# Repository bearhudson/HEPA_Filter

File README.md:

The following is from Gemini based on source generated from Claude, so I have no idea if it's correct. I am not in any way versed in fluid dynamics enough to understand if this is correct, true, or even moderately sensible. I am going to make one, which should make it self evident if it works or not by checking the filter for dinge.

--------

# Series-Stacked HEPA Purifier (Dual 140mm)

A 3D-printed, high-efficiency room air purifier utilizing a cylindrical HEPA filter and two 140mm High Static Pressure (HSP) PC fans in a series-stacked configuration. 

If you've researched DIY air purifiers online, you've likely encountered a common claim: *"PC fans cannot push air through a HEPA filter because they don't generate enough static pressure."* 

This README breaks down the fluid dynamics and math proving why that claim is based on a misunderstanding of system impedance, and how series-stacking, swirl recovery, and acoustic tuning solve the problem.

---

## The Myth: "PC Fans Lack the Pressure for HEPA"

The skepticism online stems from comparing two mismatched static figures:
1. **The Filter's Rated Pressure Drop:** A standard pleated filter might list a pressure drop of $250 \text{ Pa}$ ($1.0 \text{ mmH}_2\text{O}$).
2. **The Fan's Rated Static Pressure:** A premium 140mm PC fan might max out at $25 \text{ Pa}$ ($2.5 \text{ mmH}_2\text{O}$).

If $25 \text{ Pa} < 250 \text{ Pa}$, the fan stalls, right? **Wrong.** 

This assumes the filter's pressure drop is a static, unchanging wall. In reality, a filter's resistance is a curve that depends entirely on airflow. The $250 \text{ Pa}$ rating is usually calculated at an HVAC system's flow rate of **300+ CFM**. We are targeting **40 to 60 CFM** for a single room.

### 1. The Math of Filter Resistance (System Impedance)
Airflow through the densely packed micro-glass fibers of a HEPA filter is strictly in the **laminar flow regime**. According to Darcy's Law for porous media, pressure drop ($\Delta P$) in laminar flow scales *linearly* with velocity (and therefore volumetric flow rate, $Q$):

$$ \Delta P = R \cdot Q $$

If a filter creates $250 \text{ Pa}$ of resistance at $300 \text{ CFM}$, we can find its resistance coefficient ($R$):

$$ R = \frac{250 \text{ Pa}}{300 \text{ CFM}} = 0.833 \text{ Pa/CFM} $$

If we only need $60 \text{ CFM}$ to achieve 4.5 Air Changes per Hour (ACH) in a 100 sq ft room, the actual pressure drop we must overcome is:

$$ \Delta P_{target} = 0.833 \cdot 60 = 50 \text{ Pa} $$

A single 140mm PC fan maxing out at $25 \text{ Pa}$ still cannot overcome this. This is where the series stack comes in.

### 2. The Math of Series Stacking
When fans are placed side-by-side (parallel), their volumetric flow ($Q$) adds together, but their pressure limit ($\Delta P$) remains the same. When fans are placed front-to-back (**series**), their volumetric flow remains the same, but their **static pressure limits add together**.

$$ \Delta P_{total} = \Delta P_1 + \Delta P_2 $$

Two $25 \text{ Pa}$ fans in series generate a maximum static pressure of **$50 \text{ Pa}$**. 

By plotting the combined fan curve (which slopes down as flow increases) against the filter's linear impedance curve (which slopes up as flow increases), the lines intersect at the **Operating Point**. Two 140mm HSP fans in series shift the pressure curve high enough to intersect the filter's impedance curve right at our $40 \text{-} 60 \text{ CFM}$ target.

---

## Aerodynamic Optimizations

Brute-forcing pressure isn't enough; the air must be managed efficiently to prevent turbulence and stalling. This design incorporates three specific aerodynamic features:

### The 12-Degree Diffuser
Air exiting the $94\text{ mm}$ inner bore of the filter must expand to hit the $132\text{ mm}$ swept area of the 140mm fans. If the transition is an abrupt flat step, flow separates, creating a low-pressure vortex that acts like a solid wall, artificially increasing system impedance. 
* This design uses a **$12^\circ$ half-angle conical diffuser**. Fluid dynamics dictates that a divergence angle under $15^\circ$ prevents boundary layer separation, allowing kinetic energy to efficiently convert back to static pressure before hitting the first fan.

### The Swirl Straightener
Axial fans impart a corkscrew rotation (swirl) to the air. If Fan 1 feeds directly into Fan 2, Fan 2's blades are hitting air that is already rotating in the same direction. This effectively reduces Fan 2's relative angle of attack to zero, rendering it useless. 
* Between the two fans is a **16mm deep, 13-vane stator**. It recovers the rotational kinetic energy of Fan 1, converting it into axial static pressure, and feeds non-rotating air into Fan 2 so it can bite the air and multiply the pressure curve properly. (13 is a prime number to prevent harmonic tonal resonance with standard 7- or 9-blade fan rotors).

### Acoustic Tuning (PWM Offset)
When two identical motors spin at the exact same RPM in a shared structural tube, they drift in and out of phase, creating a loud, pulsing harmonic hum (beating). 
* The custom ESP32 firmware drives the two fans on independent PWM channels. Fan 2 is mathematically offset to run **10% faster** than Fan 1. This prevents phase-locking and completely eliminates the beating frequency, resulting in a smooth, steady white noise.

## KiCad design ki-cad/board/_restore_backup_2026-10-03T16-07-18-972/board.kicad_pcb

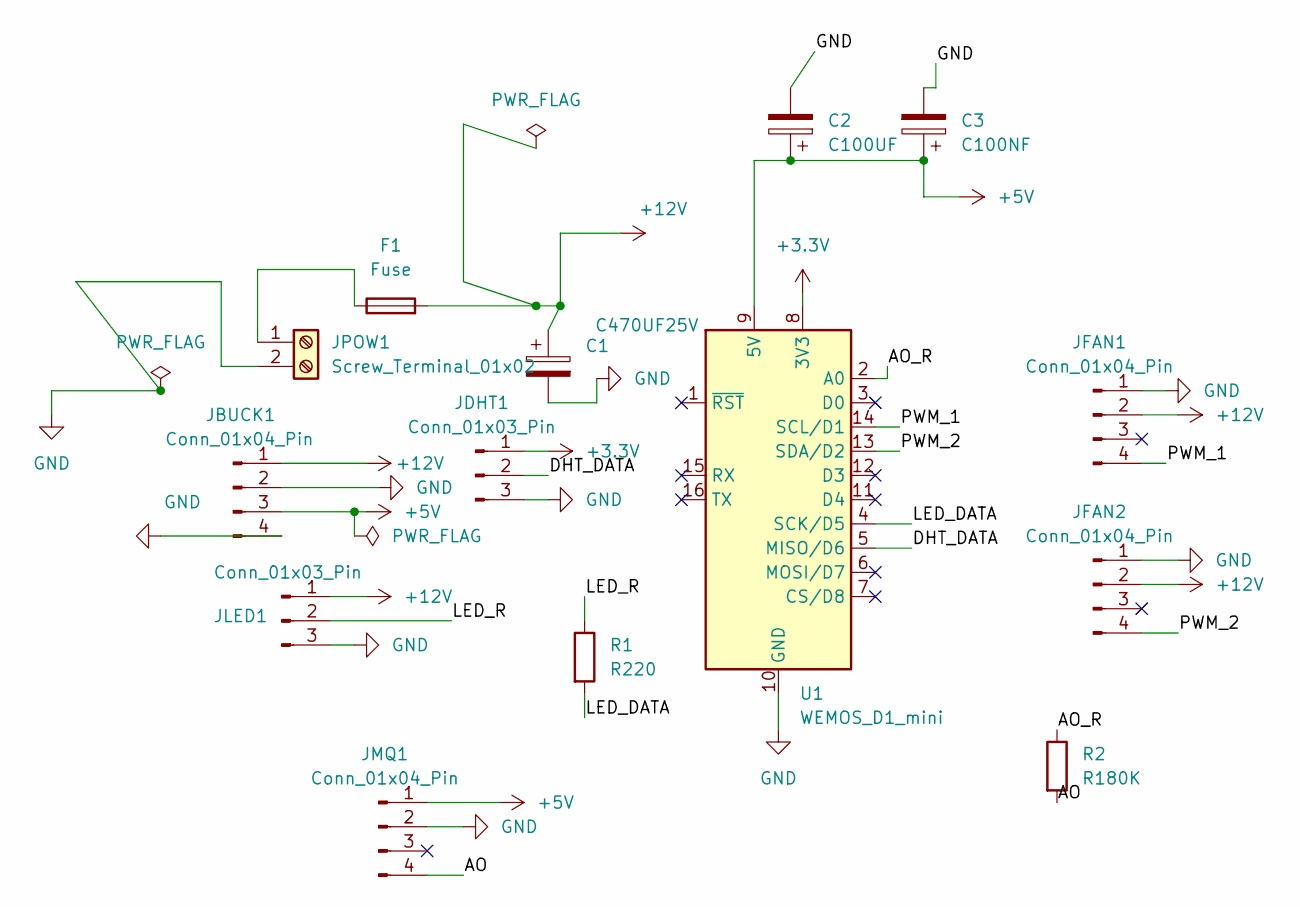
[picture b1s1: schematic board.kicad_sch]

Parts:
C1: C470UF25V; CP_Radial_D8.0mm_P3.50mm
C2: C100UF; CP_Radial_D8.0mm_P3.50mm
C3: C100NF; C_Disc_D4.3mm_W1.9mm_P5.00mm
F1: Fuse; Fuseholder_Blade_ATO_Littelfuse_Pudenz_2_Pin
JBUCK1: Conn_01x04_Pin; PinHeader_1x04_P2.54mm_Vertical
JDHT1: Conn_01x03_Pin; PinHeader_1x03_P2.54mm_Vertical
JFAN1, JFAN2: Conn_01x04_Pin; FanPinHeader_1x04_P2.54mm_Vertical
JLED1: Conn_01x03_Pin; JST_XH_B3B-XH-A_1x03_P2.50mm_Vertical
JMQ1: Conn_01x04_Pin; PinHeader_1x04_P2.54mm_Vertical
JPOW1: Screw_Terminal_01x02; TerminalBlock_Phoenix_MKDS-1,5-2-5.08_1x02_P5.08mm_Horizont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
R1: R220; R_Axial_DIN0207_L6.3mm_D2.5mm_P7.62mm_Horizontal
R2: R180K; R_Axial_DIN0207_L6.3mm_D2.5mm_P7.62mm_Horizontal
U1: WEMOS_D1_mini; WEMOS_D1_mini_light

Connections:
+3.3V: JDHT1.1, U1.8 (3V3)
+5V: C2.1, C3.1, JBUCK1.3, JMQ1.1, U1.9 (5V)
+12V: C1.1, F1.2, JBUCK1.1, JFAN1.2, JFAN2.2, JLED1.1
/AO: JMQ1.4, R2.2
/AO_R: R2.1, U1.2 (A0)
/DHT_DATA: JDHT1.2, U1.5 (MISO/D6)
/LED_DATA: R1.2, U1.4 (SCK/D5)
/LED_R: JLED1.2, R1.1
/PWM_1: JFAN1.4, U1.14 (SCL/D1)
/PWM_2: JFAN2.4, U1.13 (SDA/D2)
GND: C1.2, C2.2, C3.2, JBUCK1.2, JBUCK1.4, JDHT1.3, JFAN1.1, JFAN2.1, JLED1.3, JMQ1.2, JPOW1.2, U1.10 (GND)
unnamed: F1.1, JPOW1.1

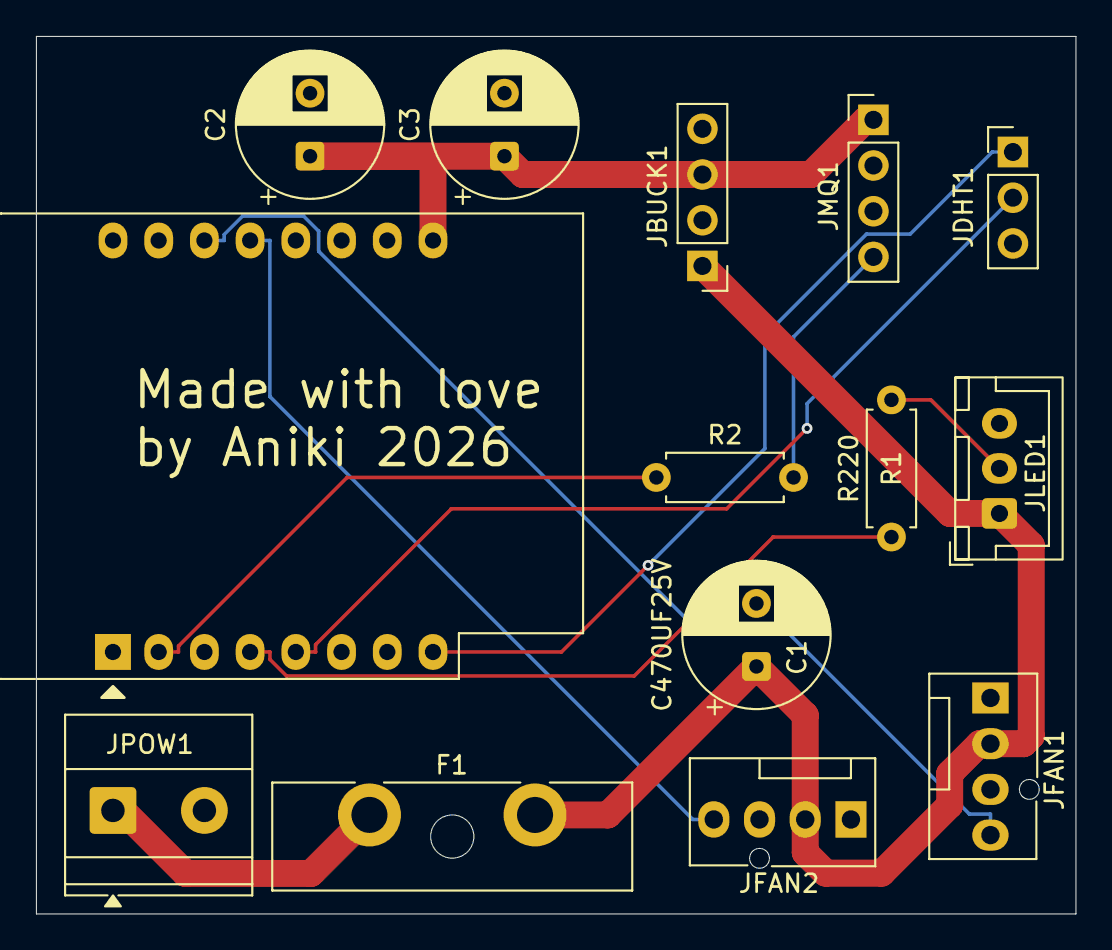
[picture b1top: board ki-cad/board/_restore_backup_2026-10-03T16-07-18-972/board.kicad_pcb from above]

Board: 2 copper layers, 57.8 x 48.8 mm, 14 parts (0 on the bottom side), 12 nets.

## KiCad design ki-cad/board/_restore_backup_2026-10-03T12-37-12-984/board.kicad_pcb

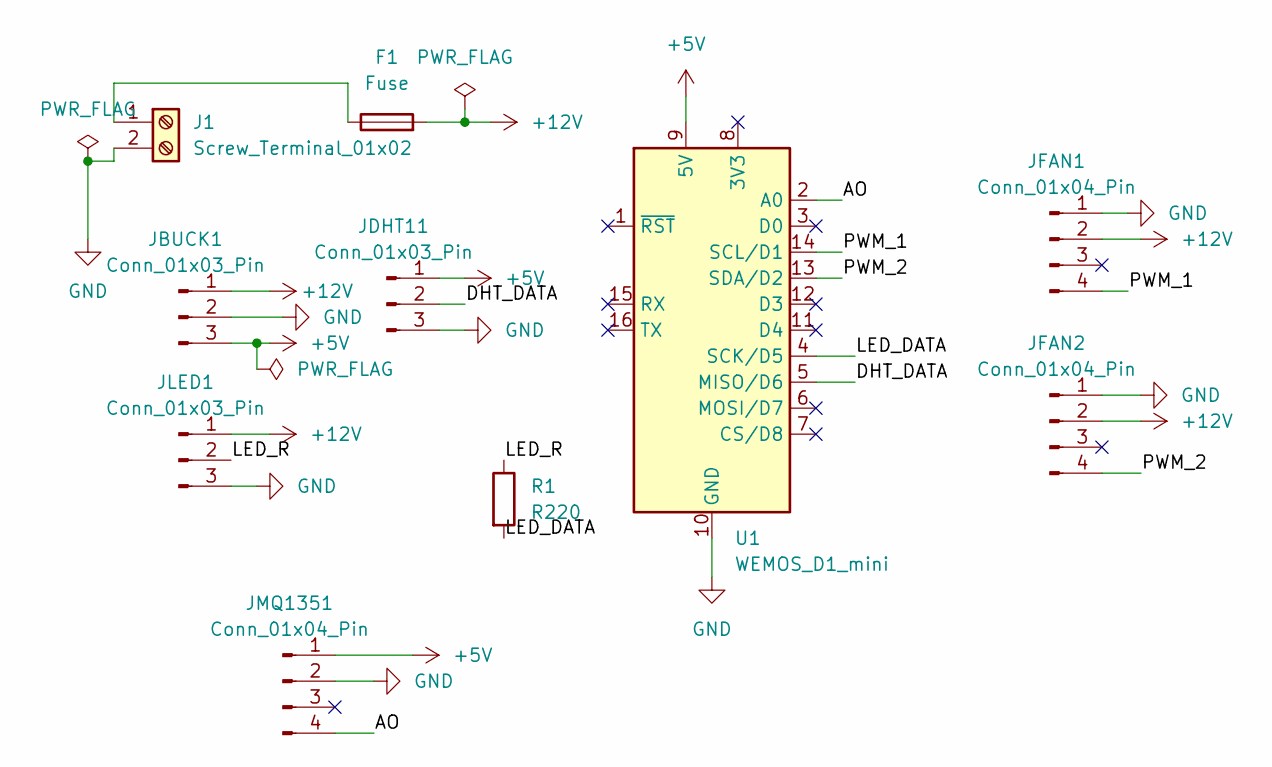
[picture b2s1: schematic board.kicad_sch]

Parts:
F1: Fuse; Fuse_Blade_ATO_directSolder
J1: Screw_Terminal_01x02; TerminalBlock_Phoenix_MKDS-1,5-2-5.08_1x02_P5.08mm_Horizont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
JBUCK1: Conn_01x03_Pin; PinHeader_1x03_P2.54mm_Vertical
JDHT11: Conn_01x03_Pin; PinHeader_1x03_P2.54mm_Vertical
JFAN1, JFAN2: Conn_01x04_Pin; Molex_KK-254_AE-6410-04A_1x04_P2.54mm_Vertical
JLED1: Conn_01x03_Pin; PinHeader_1x03_P2.54mm_Vertical
JMQ1351: Conn_01x04_Pin; PinHeader_1x04_P2.54mm_Vertical
R1: R220; R_Axial_DIN0207_L6.3mm_D2.5mm_P7.62mm_Horizontal
U1: WEMOS_D1_mini; WEMOS_D1_mini_light

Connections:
+5V: JBUCK1.3, JDHT11.1, JMQ1351.1, U1.9 (5V)
+12V: F1.2, JBUCK1.1, JFAN1.2, JFAN2.2, JLED1.1
/AO: JMQ1351.4, U1.2 (A0)
/DHT_DATA: JDHT11.2, U1.5 (MISO/D6)
/LED_DATA: R1.2, U1.4 (SCK/D5)
/LED_R: JLED1.2, R1.1
/PWM_1: JFAN1.4, U1.14 (SCL/D1)
/PWM_2: JFAN2.4, U1.13 (SDA/D2)
GND: J1.2, JBUCK1.2, JDHT11.3, JFAN1.1, JFAN2.1, JLED1.3, JMQ1351.2, U1.10 (GND)
unnamed: F1.1, J1.1

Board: 2 copper layers, 10 parts (0 on the bottom side), 10 nets, no tracks yet.
